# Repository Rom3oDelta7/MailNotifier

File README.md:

# MailNotifier
Hardware and software solution to be notified when your mail arrives

This is a simple system that will notify you when your mailbox has been delivered.
You get a notification for the first opening (mail delivered) and the second (mail collected).
These notifications will be sent to your phone using both Blynk and SMS text.
If you have an Apple Watch, the notification will be displayed on the watch as well (see picture above).
The Blynk dashboard provides more information and options, including the date and time the mail was delivered,
what the operating hours are, and status LEDs.

Since the wiring was already in place for my home
I designed this with a wired connection to my mailbox using a standard magnetic reed switch such as that found in
security systems.
Any normally closed switch can be used to sense when the mailbox is open.
If your installation requires a normally open switch instead,
there is a single define in the code that allows you to change the sense.

See more about this projects on [hackster.io].

## Hardware

The hardware is quite simple. 
A WeMOS D1 R2 Mini (ESP8266) is used as the controller. There are just 3 connections:
1. the reed switch (which should be normally closed (e.g. magnet is engaged)), and
1. a status LED
1. 5V DV power

The system requires a 5V 1A DC power supply.

Earlier versions of this system suffered from EMI (electromagnetic interference) when lightning stuck nearby
(a common occurrence during the summer monsoons) due in part to a long wire out to the mailbox acting as an antenna.
In Rev B hardware (and Rev 2 software), this issue is handled sensing the switch differently to distinguish an open event from EMI.
Moreover, the lightning-caused high-voltage EMI over time caused the input port to go deaf requiring replacement of the MCU.
Rev B hardware insulates the ESP8266 input port from the external line with a diode and a MOSFET;
these parts have much higher voltage tolerances are easier and cheaper to replace than the ESP8266 MCU module.

PCBs may be ordered from PCBs.io at https://PCBs.io/share/49aNb.

## User Interface

The user interface is shown below:

* The "READY" LED (green) indicates that the mailbox is currently closed.
Note that the ready light will not be on outside operating hours (see below).
* The "OPENED" LED (red) indicates that the mailbox has been opened.
* The "CLLCTD" LED (blue) indicates that the mail has been collected.
This is a heuristic: it is activated if the mailbox is opened _again_ after 10 minutes.
* "DATE" and "TIME" indicate the date (YYYY.MM.DD) and time (24 hr) the mailbox was first opened.
If the mailbox is opened multiple times, the date & time do _not_ change;
you must reset the system (see below) to clear the date & time and reset the indicators.
* The "STOP/START" field is used to set operating hours.
The default is 1100 to 2000 hours.
* "IGNORED" indicates how many times the mailbox was opened outside operating hours.
* The "RESET" button resets the LEDs and the date & time displays.
Note that the system will reset itself automatically at midnight each day.
* The "REBOOT" slider is used to reboot the system.
To reboot, slide the switch all the way to the right.
You have 5 seconds to change your mind and slide it back to the left.
The "READY" LED will extinguish, a message about canceling the reboot will appear in the DATE and TIME displays,
and the system will reboot after a 5 second delay.
Note that this mechanism can also be used to ensure the end-to-end system is running: if the reboot message comes up
this indicates the system is active - just quickly slide the switch back to the left.

Note that all of the built-in delays and timing heuristics can be easily personalized by changing the C++ preprocessor defines in the sketch.

## Firmware

The C++ code uses the [Blynk] service. 
You must first download the Blynk app for your smartphone (iOS or Android) and sign up for the service.
You can then download this app from within Blynk using the QR code in the "Blynk" folder.

See the [Blynk getting started guide].

The code uses the [Blynk Library], my [NTP (Network Time Protocol) clock library], and Paul Stoffregen's [Time Library].
Be sure to change the "auth", "SSID", and "password" strings
and set the email address string to the [address your carrier uses to send an SMS to your phone] in the file "locals.h". 
In the sketch file, set the parameter to the

```C++
NTP_UTC_Timezone()
```

function to your local timezone. 
See ```WorldTimezones.h``` in the [NTP (Network Time Protocol) clock library] for details and
a list of timezones you can set.

The code may be updated using OTA (Over The Air) updates.
You can still upload the code in the traditional USB approach, but after the firmware has been uploaded for the first time
you can upload subsequent updates over WiFi. 
See the [ESP8266 OTA update documentation] for details.

__Important__: access to the current time is fundamental to the operation of the system.
Therefore, you must have Internet access for the NTP library to work. 

## Enclosure

The STL files to 3D print the enclosure are included in the repo:
one file for the base and one for the lid.
The wiring I piggybacked onto to reach my mailbox happens to come into a patch panel,
so I have an RJ45 jack opening in my enclosure, which is what you see in the picture. 
In your slicing software you should turn on support for the RJ45 opening.
Just about any filament is fine - I used PLA with a layer height of 0.4mm. 
The HEX address you see on the label is the unit address fro OTA updates.

## Implementation

### Assembly

* 3D print the enclosure base and lid.
* Assemble the discrete components to the PCB.
* Solder the female headers that come with the WeMOS to the PCB.
* If using the RJ45 connector, punch down the switch connection wires into the RJ45 keystone connector,
leaving enough wire to comfortably reach the PCB.
Then insert the RJ45 into the case.
* Solder the connection for the LED and use some 2mm shrink wrap tubing to protect the leads from shorting
(or electrical tape if you don't have this).
* Mount the LED.
The hole is sized for a 3mm LED. If the fit is too loose, then secure the LED to the case with some
UV-curable resin (preferred) or hot melt glue.
If you don't use a green LED, you should recalculate the value of the current limiting resistor
to match the Vf of your LED.
If you don't know what this means, just use a green LED.
* Solder the power wires to the DC power jack and fasten to the case.
* Solder the wires to the PCB: power, switch, and LED, being sure to observe the correct polarity (marked on the PCB).
* Insert the WeMOS into the headers.
__Note:__ You can mount the PCB to the enclosure now, but you will probably find it easier to program it first
(see below).
* Fasten the board to the mounting post in the base of the enclosure.
* Attach the lid using the flat head screws.

### Programming

* Ensure the aforementioned local/personal changes have been implemented in the sketch (.ino) file and "locals.h".
* For the first upload, connect a microUSB plug to the WeMOS.
* In the Arduino IDE, select the "LOLIN(WeMos)D1 R2 & Mini" board.
* Board settings:

|Parameter|Setting|
|---|---|
|CPU Frequency|160 MHz|
|Flash Size|4M(1M SPIFFS)|
|Upload SPeed|921600|
|Port|_your USB serial port_|

* The WeMOS has an automatic system for enabling the flash sequence so no buttons need to be pressed.
* After the code is uploaded, the green LED will illuminate when all of the setup and initialization steps are complete.
* While the serial cable is still connected, open the serial port (115200 baud) and reset the WeMOS.
The HEX address you need to do OTA updates will be printed.
Save this for future use.
At this point, you can launch the Blynk app and run the notifier app dashboard. 
* The USB cable may now be removed.

# Copyright

Copyright 2018 Rob Redford.
This work is licensed under the Creative Commons Attribution-ShareAlike 4.0 International License.
To view a copy of this license, visit [CC-BY-SA].

[hackster.io] https://www.hackster.io/Rom3oDelta7/smartphone-mailbox-notifier-version-2-sept-2018-822a1d
[Blynk]: http://www.blynk.cc/
[Blynk Library]: http://www.blynk.cc/getting-started/
[Blynk getting started guide]: http://www.blynk.cc/getting-started/
[NTP (Network Time Protocol) clock library]: https://github.com/Rom3oDelta7/NTP-RTC
[Time Library]: http://www.pjrc.com/teensy/td_libs_Time.html
[ESP8266 OTA update documentation]: https://arduino-esp8266.readthedocs.io/en/latest/ota_updates/readme.html
[address your carrier uses to send an SMS to your phone]: http://www.digitaltrends.com/mobile/how-to-send-e-mail-to-sms-text/
[CC-BY-SA]: https://creativecommons.org/licenses/by-sa/4.0/

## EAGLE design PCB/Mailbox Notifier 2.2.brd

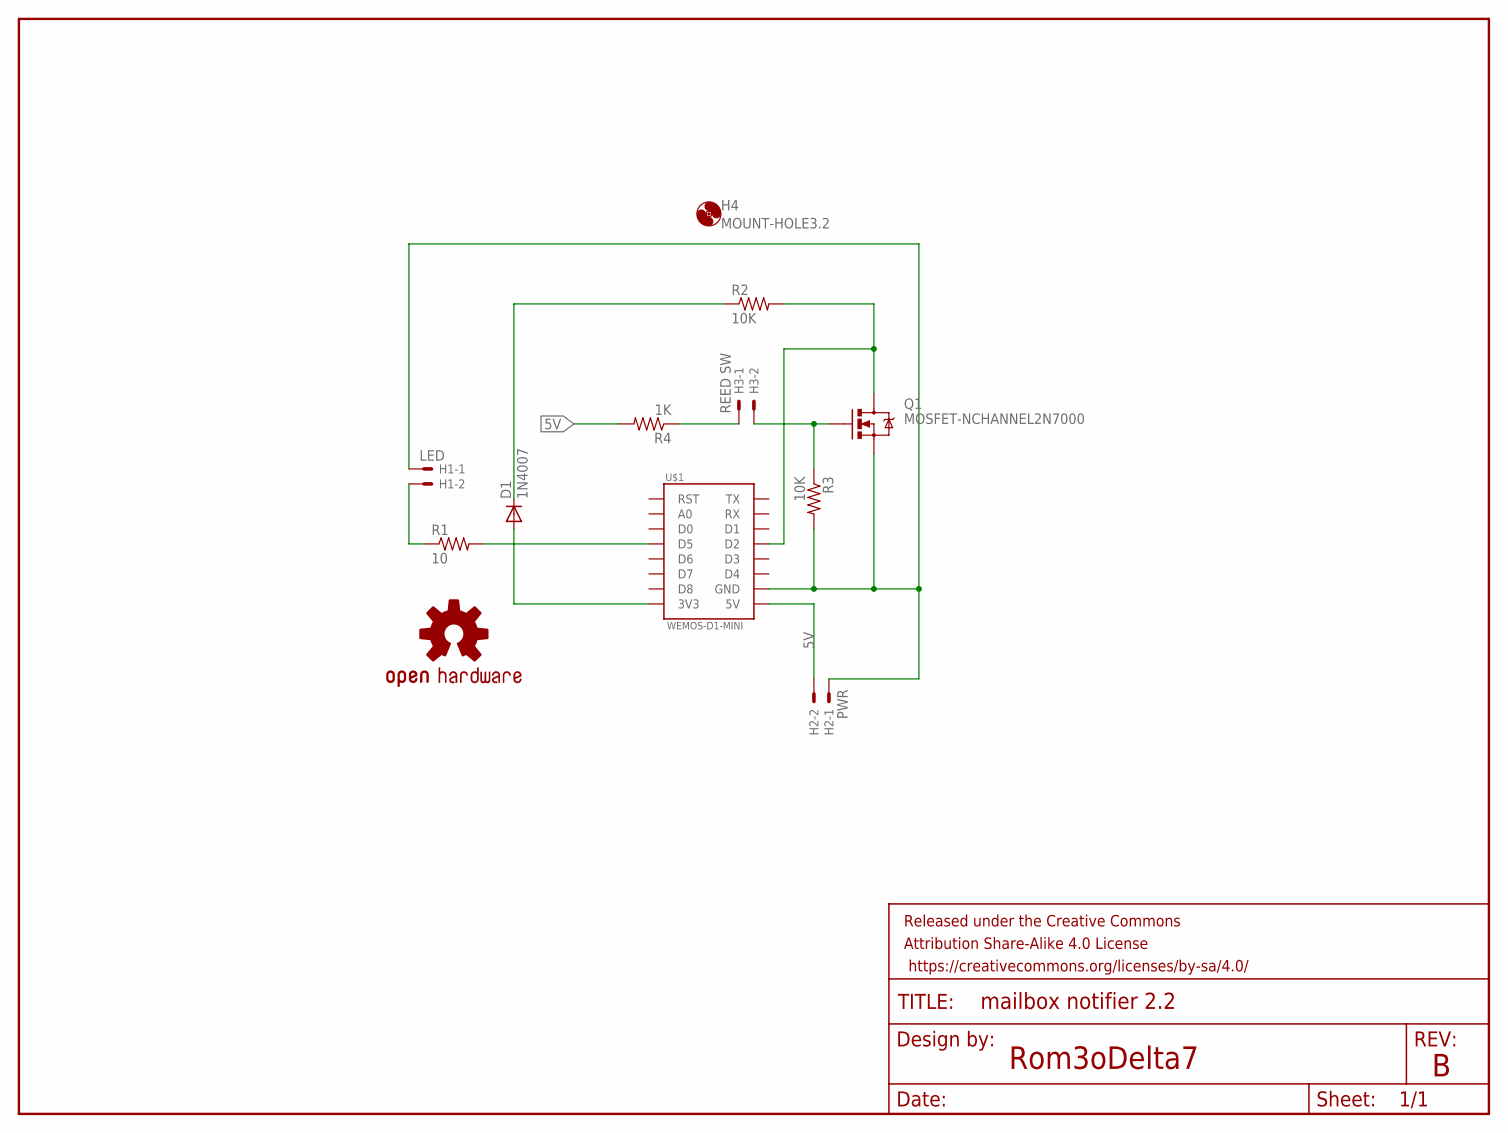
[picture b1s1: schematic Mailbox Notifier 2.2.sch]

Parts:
D1: 1N4007; DO41-10
FRAME1: FRAME-LETTER; CREATIVE_COMMONS
H1: LED; 22-23-2021
H2: PWR; 22-23-2021
H3: REED SW; 22-23-2021
H4: MOUNT-HOLE3.2; 3,2
LOGO1: OSHW-LOGOMINI; OSHW-LOGO-MINI
Q1: MOSFET-NCHANNEL2N7000; TO-92
R1: 10; AXIAL-0.5
R2, R3: 10K; AXIAL-0.4
R4: 1K; AXIAL-0.4
U$1: WEMOS-D1-MINI

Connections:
5V: H2.2, R4.P$2 (2), U$1.5V
GND: H1.1, H2.1, Q1.1 (S), R3.P$2 (2), U$1.GND
unnamed: D1.A, U$1.3V3
unnamed: H3.2, Q1.2 (G), R3.P$1 (1)
unnamed: R1.P$2 (2), U$1.D5
unnamed: H1.2, R1.P$1 (1)
unnamed: Q1.3 (D), R2.P$2 (2), U$1.D2
unnamed: D1.C, R2.P$1 (1)
unnamed: H3.1, R4.P$1 (1)

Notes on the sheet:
Rom3oDelta7

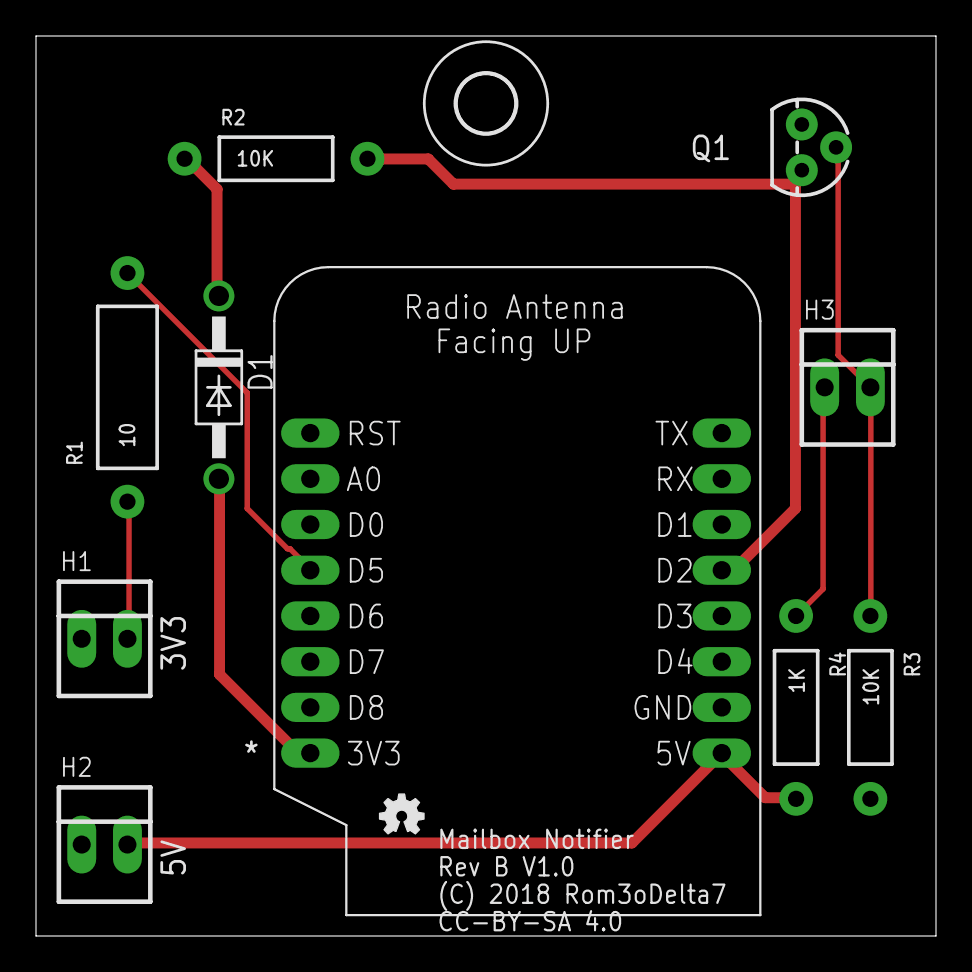
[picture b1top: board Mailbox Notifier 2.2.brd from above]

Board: 2 copper layers, 50.0 x 50.0 mm, 13 parts (0 on the bottom side), 9 nets.

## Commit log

2018-09-11 Initial checkin RevB/2
2018-09-11 Incomplete first draft
2018-09-11 photos for readme
2018-09-11 Next draft
2018-09-11 Final Eagle files
2018-09-11 Add copyright notice
2018-09-11 Reconcile copyrights
2018-09-11 1. code cleanup 2. count open cycles during the post-delvery lockout as ignored events
2018-09-11 bill of materia;s
2018-09-20 Fix incorrect pin definitionsleft over from Rev A hardware
2018-09-22 update build instructions to current board name (LOLIN(WeMos)D1 R2 & Mini)) update comments in sketch
2018-09-22 add photo of assembled unit
2018-09-22 add assembled image photo link to README
2018-09-22 note that Blynk watch app is not currently available
2018-09-22 i hate it when I do that :-(
2018-09-23 Clarify Apple Watch notifications
2018-09-24 Update README, add hackster.io project link, and add missing diode to BOM
2018-09-26 When outside operating hours an open mailbox was being counted multiple times when opened (each loop iteration while the mailbox was open). Add some simple logic to count cycles (open->close) instead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

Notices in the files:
PCB/Mailbox Notifier 2.2.brd:
(C) 2018 Rom3oDelta7
CC-BY-SA 4.0
parts and their libraries:
SparkFun-Aesthetics: Licensing: Creative Commons ShareAlike 4.0 International - https://creativecommons.org/licenses/by-sa/4.0
SparkFun-Aesthetics: Released under the Creative Commons Attribution Share-Alike 4.0 License
SparkFun-Aesthetics: Released under the Creative Commons
